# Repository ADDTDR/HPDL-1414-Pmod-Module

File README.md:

Assembled board v1 
|   |   |
| - | - |  
|   |  |
|  | |
|  | |
|| | 
|  | |

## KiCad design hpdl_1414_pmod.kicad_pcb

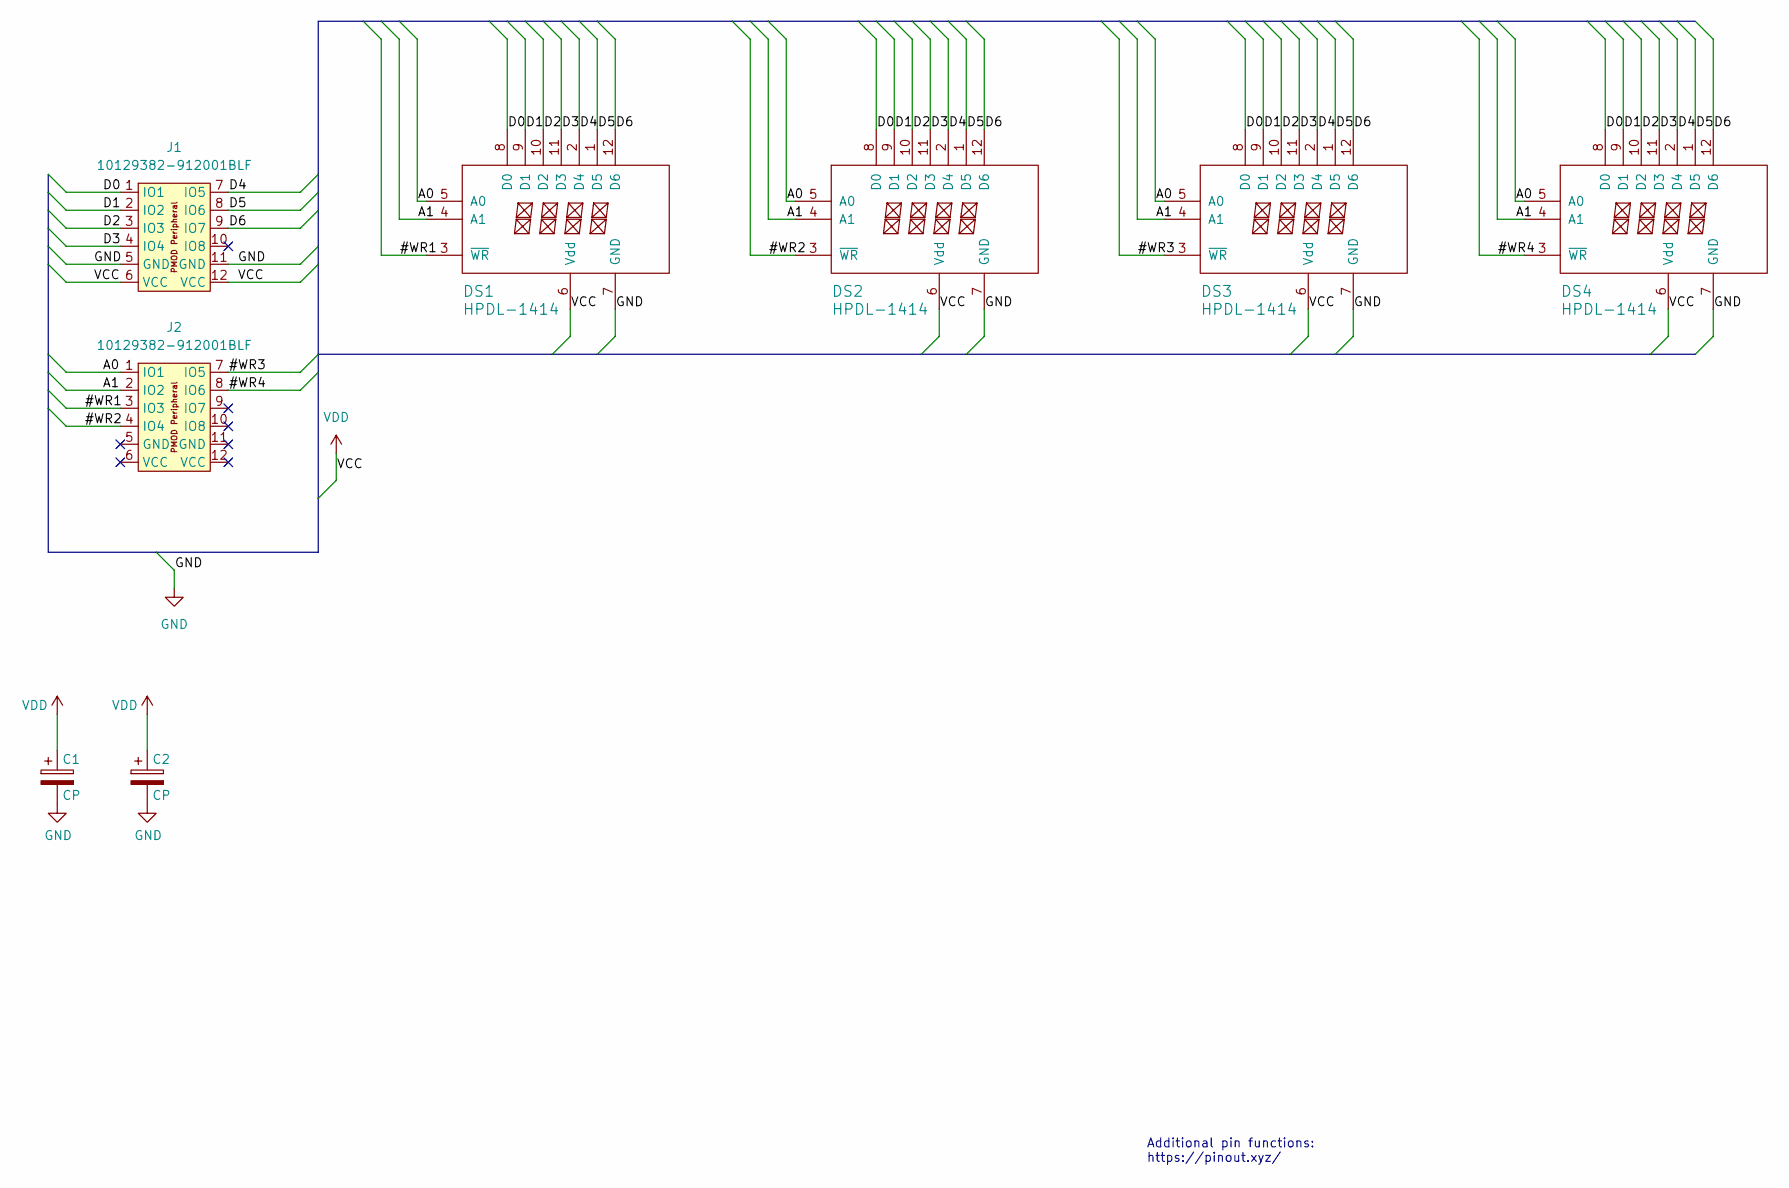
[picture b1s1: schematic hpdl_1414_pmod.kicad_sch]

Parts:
C1, C2: CP; C_Disc_D4.3mm_W1.9mm_P5.00mm
DS1, DS2, DS3, DS4: HPDL-1414; hpdl-1414
J1, J2: 10129382-912001BLF; PinHeader_2x06_P2.54mm_PMODPeriph2B; LCSC Part C492434

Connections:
/#WR1: DS1.3 (~WR), J2.3 (IO3)
/#WR2: DS2.3 (~WR), J2.4 (IO4)
/#WR3: DS3.3 (~WR), J2.7 (IO5)
/#WR4: DS4.3 (~WR), J2.8 (IO6)
/A0: DS1.5 (A0), DS2.5 (A0), DS3.5 (A0), DS4.5 (A0), J2.1 (IO1)
/A1: DS1.4 (A1), DS2.4 (A1), DS3.4 (A1), DS4.4 (A1), J2.2 (IO2)
/D0: DS1.8 (D0), DS2.8 (D0), DS3.8 (D0), DS4.8 (D0), J1.1 (IO1)
/D1: DS1.9 (D1), DS2.9 (D1), DS3.9 (D1), DS4.9 (D1), J1.2 (IO2)
/D2: DS1.10 (D2), DS2.10 (D2), DS3.10 (D2), DS4.10 (D2), J1.3 (IO3)
/D3: DS1.11 (D3), DS2.11 (D3), DS3.11 (D3), DS4.11 (D3), J1.4 (IO4)
/D4: DS1.2 (D4), DS2.2 (D4), DS3.2 (D4), DS4.2 (D4), J1.7 (IO5)
/D5: DS1.1 (D5), DS2.1 (D5), DS3.1 (D5), DS4.1 (D5), J1.8 (IO6)
/D6: DS1.12 (D6), DS2.12 (D6), DS3.12 (D6), DS4.12 (D6), J1.9 (IO7)
GND: C1.2, C2.2, DS1.7 (GND), DS2.7 (GND), DS3.7 (GND), DS4.7 (GND), J1.5 (GND), J1.11 (GND)
VDD: C1.1, C2.1, DS1.6 (Vdd), DS2.6 (Vdd), DS3.6 (Vdd), DS4.6 (Vdd), J1.6 (VCC), J1.12 (VCC)

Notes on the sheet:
Additional pin functions: https://pinout.xyz/

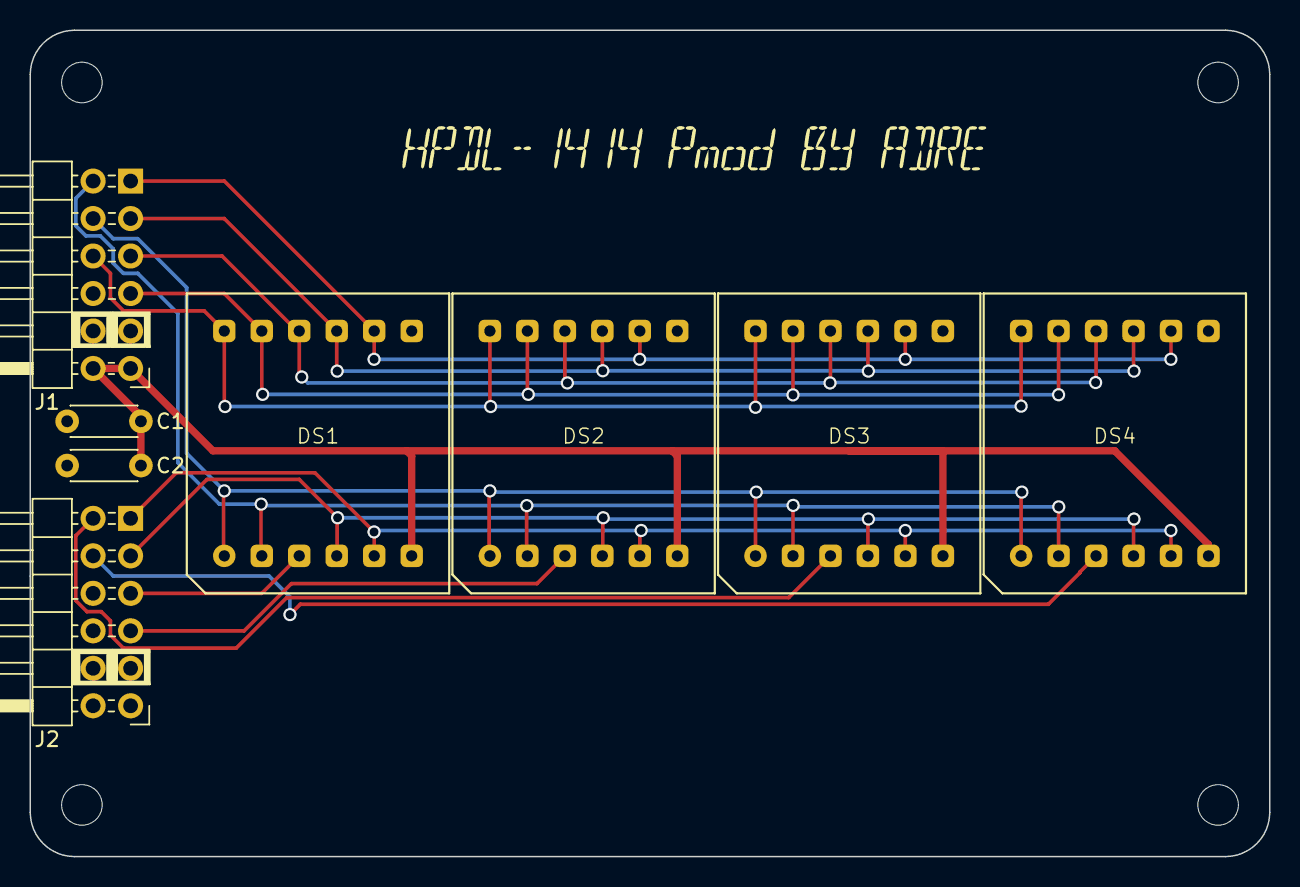
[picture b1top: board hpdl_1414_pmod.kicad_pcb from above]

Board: 2 copper layers, 84.0 x 56.0 mm, 8 parts (0 on the bottom side), 15 nets.

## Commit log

2024-09-18 Change pcb mounting hole type
2024-09-19 Finilize shematic, place components, add 3d models
2024-09-19 Grenerate gerbers, V1.0
2024-10-14 Add Readme and assembled board images
2024-12-19 Add arduino sketch
2024-12-19 Add code
2024-12-19 Clean out unused code
2025-01-03 Simple itaration of 1 display place from bram data
2025-01-04 Ok, but order
2025-01-04 Add Verilog usage example
2025-01-06 Add uart verilog module, circular print on display
2025-01-07 Push text to the right
2025-01-07 Read data from uart and left scroll
2025-01-08 Update readme, clean out some parts of verilog code
2025-01-21 Add shift out after fill
2025-01-22 Implement backspace
2025-01-27 Fix cary glitch on backspace action if pos == 15
2025-01-28 Implement caret blinker
2025-01-30 Update repo
2025-01-30 Clean out
2025-01-30 Untrack tb out
2025-02-03 Add reset button
2025-02-04 Clean
2025-02-18 Refactor
2025-02-18 Update message
2025-02-18 Fix carry in bug
2025-02-18 Carry bug fix & update message
2025-02-19 Fix memory depth
2025-02-21 Direct memory init in the verilog file
2025-02-28 Update to kicad 9
2025-02-28 Update schematics
2025-03-02 Add reset signal
2025-03-03 Use or posedge reset
2025-03-06 Don't reset the memory state
2026-03-04 Update main module
